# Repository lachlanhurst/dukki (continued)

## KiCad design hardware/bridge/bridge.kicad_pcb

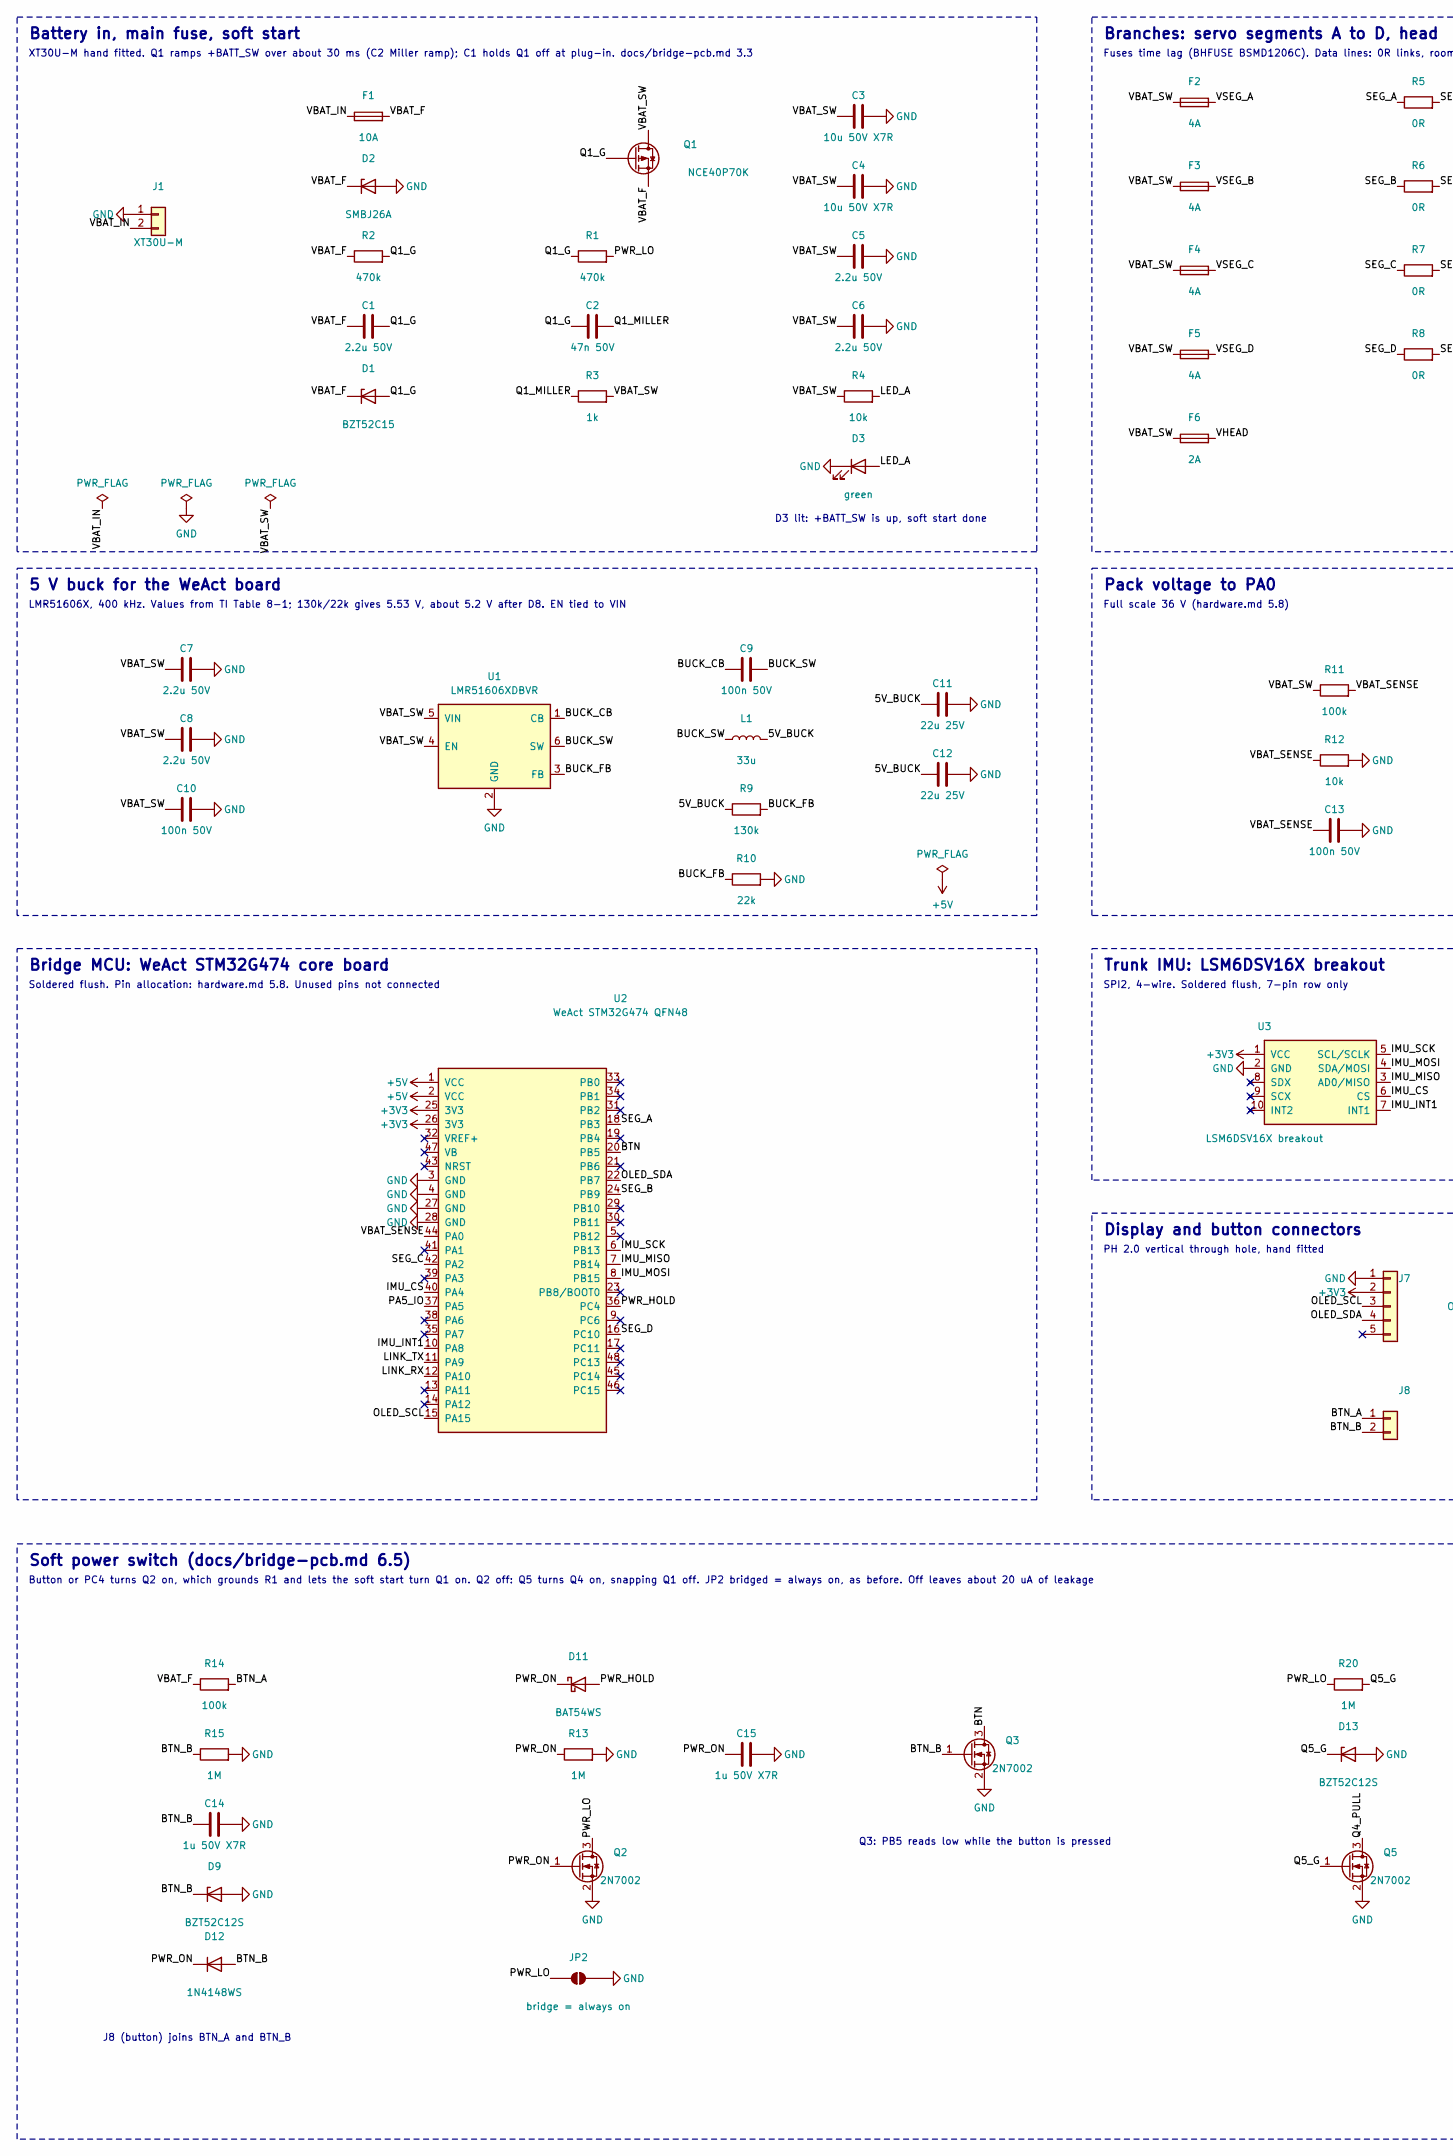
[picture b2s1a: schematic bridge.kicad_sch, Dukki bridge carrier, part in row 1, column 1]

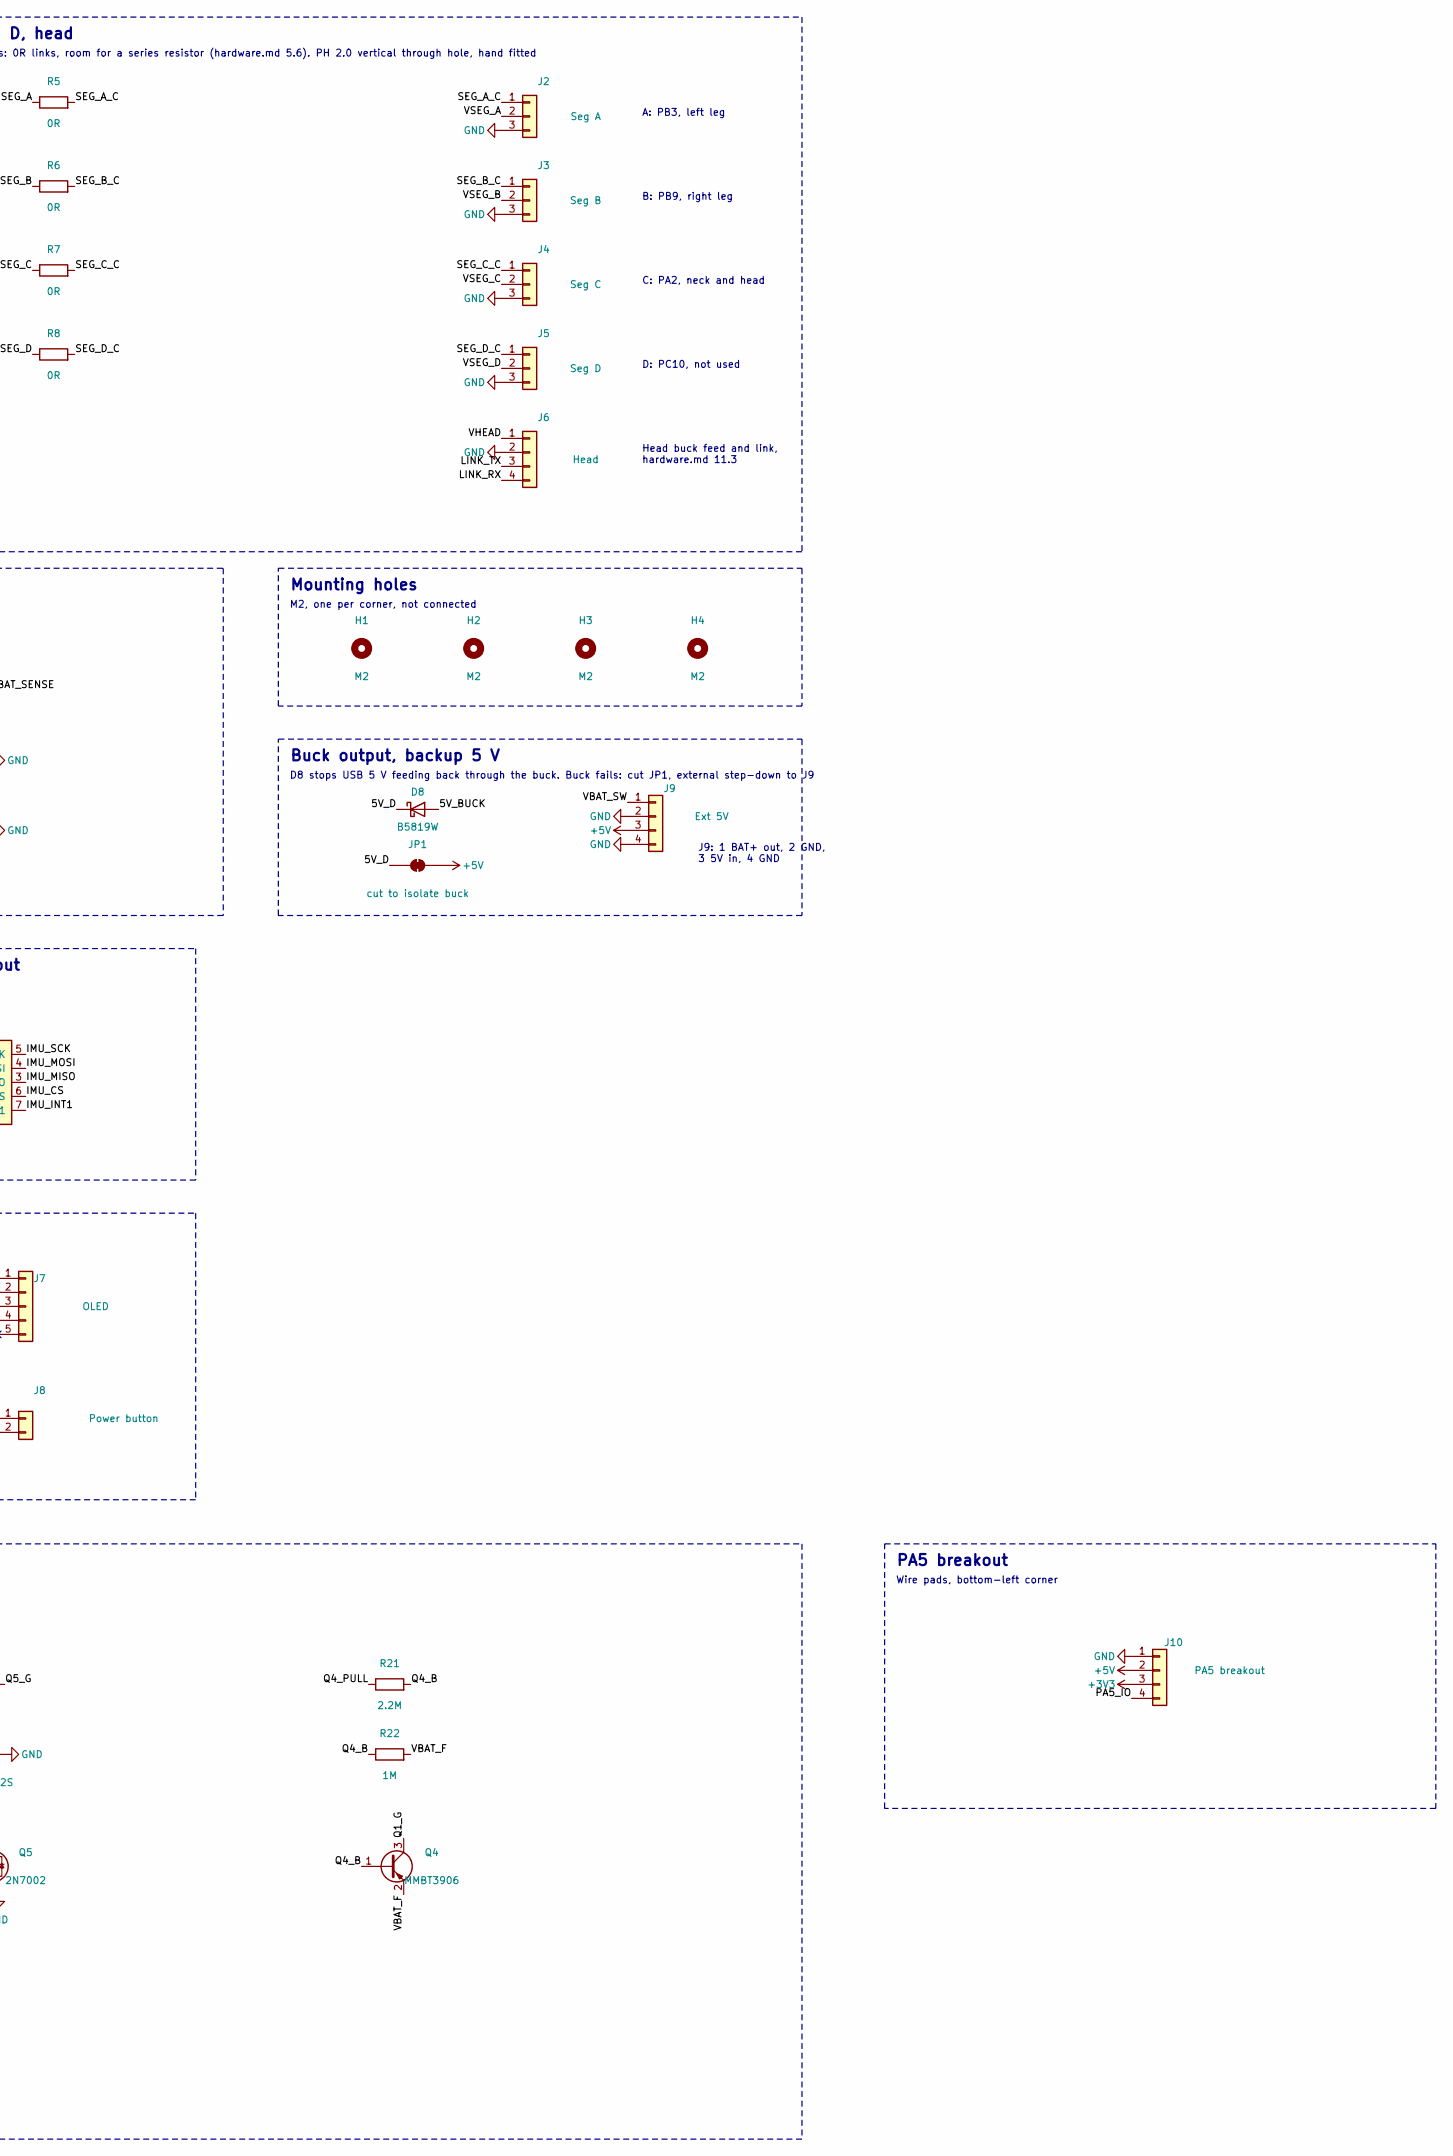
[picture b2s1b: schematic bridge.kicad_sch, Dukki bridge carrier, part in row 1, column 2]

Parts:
C1, C5, C6, C7, C8: 2.2u 50V; C_0805_2012Metric; LCSC C377773
C2: 47n 50V; C_0603_1608Metric; LCSC C1622
C3, C4: 10u 50V X7R; C_1210_3225Metric; LCSC C596319
C9, C10, C13: 100n 50V; C_0603_1608Metric; LCSC C14663
C11, C12: 22u 25V; C_0805_2012Metric; LCSC C45783
C14, C15: 1u 50V X7R; C_0805_2012Metric; LCSC C28323
D1: BZT52C15; D_SOD-123; LCSC C19077412
D2: SMBJ26A; D_SMB; LCSC C19077580
D3: green; LED_0603_1608Metric; LCSC C12624
D8: B5819W; D_SOD-123; LCSC C8598
D9, D13: BZT52C12S; D_SOD-323; LCSC C19077447
D11: BAT54WS; D_SOD-323; LCSC C7502694
D12: 1N4148WS; D_SOD-323; LCSC C2128
F1: 10A; Fuse_1206_3216Metric; MPN BHFUSE BSMD1206C-2100T, 10 A time lag, 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; LCSC C41367232
F2, F3, F4, F5: 4A; Fuse_1206_3216Metric; MPN BHFUSE BSMD1206C-1400T, 4 A time lag, 7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; LCSC C41367227
F6: 2A; Fuse_1206_3216Metric; MPN BHFUSE BSMD1206C-1200T, 2 A time lag, 7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; LCSC C41367223
H1, H2, H3, H4: M2; MountingHole_2.2mm_M2
J1: XT30U-M; AMASS_XT30U-M_1x02_P5.0mm_Vertical
J2: Seg A; JST_PH_B3B-PH-K_1x03_P2.00mm_Vertical; MPN JST B3B-PH-K-S, through hole, fitted by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
J3: Seg B; JST_PH_B3B-PH-K_1x03_P2.00mm_Vertical; MPN JST B3B-PH-K-S, through hole, fitted by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
J4: Seg C; JST_PH_B3B-PH-K_1x03_P2.00mm_Vertical; MPN JST B3B-PH-K-S, through hole, fitted by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
J5: Seg D; JST_PH_B3B-PH-K_1x03_P2.00mm_Vertical; MPN JST B3B-PH-K-S, through hole, fitted by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
J6: Head; JST_PH_B4B-PH-K_1x04_P2.00mm_Vertical; MPN JST B4B-PH-K-S, through hole, fitted by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
J7: OLED; JST_PH_B5B-PH-K_1x05_P2.00mm_Vertical; MPN JST B5B-PH-K-S, through hole, fitted by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
J8: Power button; JST_PH_B2B-PH-K_1x02_P2.00mm_Vertical; MPN JST B2B-PH-K-S, through hole, fitted by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
J9: Ext 5V; PinHeader_1x04_P2.54mm_Vertical
J10: PA5 breakout; PinHeader_1x04_P2.54mm_Vertical
JP1: cut to isolate buck; SolderJumper-2_P1.3mm_Bridged_RoundedPad1.0x1.5mm
JP2: bridge = always on; SolderJumper-2_P1.3mm_Open_RoundedPad1.0x1.5mm
L1: 33u; L_Sunlord_SWPA6045S; MPN Sunlord SWPA6045S330MT; LCSC C83451
Q1: NCE40P70K; TO-252-2; LCSC C130101
Q2, Q3, Q5: 2N7002; SOT-23; LCSC C8545
Q4: MMBT3906; SOT-23; LCSC C7420354
R1, R2: 470k; R_0603_1608Metric; LCSC C23178
R3: 1k; R_0603_1608Metric; LCSC C21190
R4, R12: 10k; R_0603_1608Metric; LCSC C25804
R5, R6, R7, R8: 0R; R_0603_1608Metric; LCSC C21189
R9: 130k; R_0603_1608Metric; LCSC C22795
R10: 22k; R_0603_1608Metric; LCSC C31850
R11, R14: 100k; R_0603_1608Metric; LCSC C25803
R13, R15, R20, R22: 1M; R_0603_1608Metric; LCSC C22935
R21: 2.2M; R_0603_1608Metric; LCSC C22938
U1: LMR51606XDBVR; SOT-23-6; LCSC C21260865
U2: WeAct STM32G474 QFN48; WeAct_STM32G474CoreBoard_QFN48
U3: LSM6DSV16X breakout; LSM6DSV16X_Breakout

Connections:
+3V3: J7.2, J10.3, U2.25 (3V3), U2.26 (3V3), U3.1 (VCC)
+5V: J9.3, J10.2, JP1.2 (B), U2.1 (VCC), U2.2 (VCC)
/5V_BUCK: C11.1, C12.1, D8.2 (A), L1.2, R9.1
/5V_D: D8.1 (K), JP1.1 (A)
/BTN: Q3.3 (D), U2.20 (PB5)
/BTN_A: J8.1, R14.2
/BTN_B: C14.1, D9.1 (K), D12.2 (A), J8.2, Q3.1 (G), R15.1
/BUCK_CB: C9.1, U1.1 (CB)
/BUCK_FB: R9.2, R10.1, U1.3 (FB)
/BUCK_SW: C9.2, L1.1, U1.6 (SW)
/IMU_CS: U2.40 (PA4), U3.6 (CS)
/IMU_INT1: U2.10 (PA8), U3.7 (INT1)
/IMU_MISO: U2.7 (PB14), U3.3 (AD0/MISO)
/IMU_MOSI: U2.8 (PB15), U3.4 (SDA/MOSI)
/IMU_SCK: U2.6 (PB13), U3.5 (SCL/SCLK)
/LED_A: D3.2 (A), R4.2
/LINK_RX: J6.4, U2.12 (PA10)
/LINK_TX: J6.3, U2.11 (PA9)
/OLED_SCL: J7.3, U2.15 (PA15)
/OLED_SDA: J7.4, U2.22 (PB7)
/PA5_IO: J10.4, U2.37 (PA5)
/PWR_HOLD: D11.2 (A), U2.36 (PC4)
/PWR_LO: JP2.1 (A), Q2.3 (D), R1.2, R20.1
/PWR_ON: C15.1, D11.1 (K), D12.1 (K), Q2.1 (G), R13.1
/Q1_G: C1.2, C2.1, D1.2 (A), Q1.1 (G), Q4.3 (C), R1.1, R2.2
/Q1_MILLER: C2.2, R3.1
/Q4_B: Q4.1 (B), R21.2, R22.1
/Q4_PULL: Q5.3 (D), R21.1
/Q5_G: D13.1 (K), Q5.1 (G), R20.2
/SEG_A: R5.1, U2.18 (PB3)
/SEG_A_C: J2.1, R5.2
/SEG_B: R6.1, U2.24 (PB9)
/SEG_B_C: J3.1, R6.2
/SEG_C: R7.1, U2.42 (PA2)
/SEG_C_C: J4.1, R7.2
/SEG_D: R8.1, U2.16 (PC10)
/SEG_D_C: J5.1, R8.2
/VBAT_F: C1.1, D1.1 (K), D2.1 (K), F1.2, Q1.3 (S), Q4.2 (E), R2.1, R14.1, R22.2
/VBAT_IN: F1.1, J1.2
/VBAT_SENSE: C13.1, R11.2, R12.1, U2.44 (PA0)
/VBAT_SW: C3.1, C4.1, C5.1, C6.1, C7.1, C8.1, C10.1, F2.1, F3.1, F4.1, F5.1, F6.1, J9.1, Q1.2 (D), R3.2, R4.1, R11.1, U1.4 (EN), U1.5 (VIN)
/VHEAD: F6.2, J6.1
/VSEG_A: F2.2, J2.2
/VSEG_B: F3.2, J3.2
/VSEG_C: F4.2, J4.2
/VSEG_D: F5.2, J5.2
GND: C3.2, C4.2, C5.2, C6.2, C7.2, C8.2, C10.2, C11.2, C12.2, C13.2, C14.2, C15.2, D2.2 (A), D3.1 (K), D9.2 (A), D13.2 (A), J1.1, J2.3, J3.3, J4.3, J5.3, J6.2, J7.1, J9.2, J9.4, J10.1, JP2.2 (B), Q2.2 (S), Q3.2 (S), Q5.2 (S), R10.2, R12.2, R13.2, R15.2, U1.2 (GND), U2.3 (GND), U2.4 (GND), U2.27 (GND), U2.28 (GND), U3.2 (GND)

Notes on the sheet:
Battery in, main fuse, soft start
XT30U-M hand fitted. Q1 ramps +BATT_SW over about 30 ms (C2 Miller ramp); C1 holds Q1 off at plug-in. docs/bridge-pcb.md 3.3
D3 lit: +BATT_SW is up, soft start done
Branches: servo segments A to D, head
Fuses time lag (BHFUSE BSMD1206C). Data lines: 0R links, room for a series resistor (hardware.md 5.6). PH 2.0 vertical through hole, hand fitted
A: PB3, left leg
B: PB9, right leg
C: PA2, neck and head
D: PC10, not used
Head buck feed and link, hardware.md 11.3
5 V buck for the WeAct board
LMR51606X, 400 kHz. Values from TI Table 8-1; 130k/22k gives 5.53 V, about 5.2 V after D8. EN tied to VIN
Pack voltage to PA0
Full scale 36 V (hardware.md 5.8)
Mounting holes
M2, one per corner, not connected
Buck output, backup 5 V
D8 stops USB 5 V feeding back through the buck. Buck fails: cut JP1, external step-down to J9
J9: 1 BAT+ out, 2 GND, 3 5V in, 4 GND
Bridge MCU: WeAct STM32G474 core board
Soldered flush. Pin allocation: hardware.md 5.8. Unused pins not connected
Trunk IMU: LSM6DSV16X breakout
SPI2, 4-wire. Soldered flush, 7-pin row only
Display and button connectors
PH 2.0 vertical through hole, hand fitted
Soft power switch (docs/bridge-pcb.md 6.5)
Button or PC4 turns Q2 on, which grounds R1 and lets the soft start turn Q1 on. Q2 off: Q5 turns Q4 on, snapping Q1 off. JP2 bridged = always on, as before. Off leaves about 20 uA of leakage
J8 (button) joins BTN_A and BTN_B
Q3: PB5 reads low while the button is pressed
PA5 breakout
Wire pads, bottom-left corner

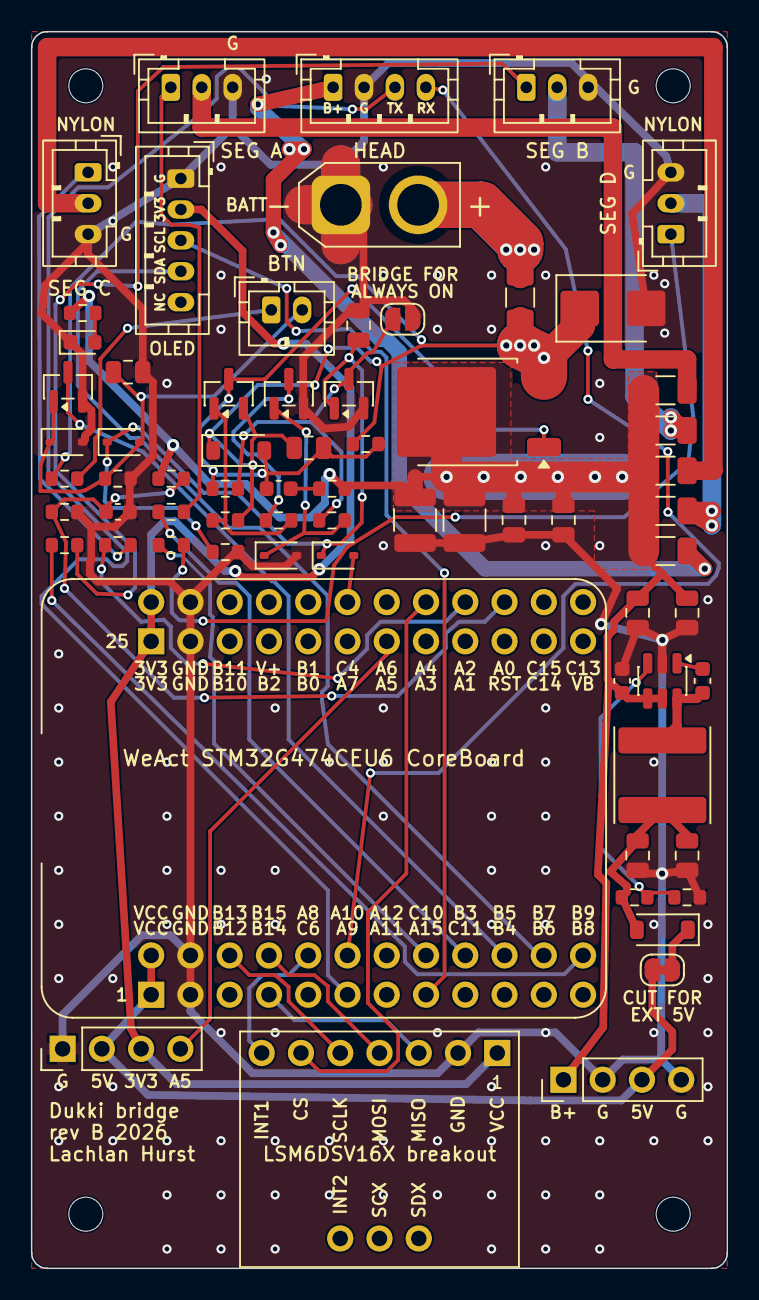
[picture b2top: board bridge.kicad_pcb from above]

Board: 2 copper layers, 45.0 x 80.0 mm, 72 parts (0 on the bottom side), 47 nets.

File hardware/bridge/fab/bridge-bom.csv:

Comment,Designator,Footprint,LCSC Part #
2.2u 50V,"C1,C5,C6,C7,C8",C_0805_2012Metric,C377773
47n 50V,C2,C_0603_1608Metric,C1622
10u 50V X7R,"C3,C4",C_1210_3225Metric,C596319
100n 50V,"C9,C10,C13",C_0603_1608Metric,C14663
22u 25V,"C11,C12",C_0805_2012Metric,C45783
1u 50V X7R,"C14,C15",C_0805_2012Metric,C28323
BZT52C15,D1,D_SOD-123,C19077412
SMBJ26A,D2,D_SMB,C19077580
green,D3,LED_0603_1608Metric,C12624
B5819W,D8,D_SOD-123,C8598
BZT52C12S,"D9,D13",D_SOD-323,C19077447
BAT54WS,D11,D_SOD-323,C7502694
1N4148WS,D12,D_SOD-323,C2128
10A,F1,Fuse_1206_3216Metric,C41367232
4A,"F2,F3,F4,F5",Fuse_1206_3216Metric,C41367227
2A,F6,Fuse_1206_3216Metric,C41367223
33u,L1,L_Sunlord_SWPA6045S,C83451
NCE40P70K,Q1,TO-252-2,C130101
2N7002,"Q2,Q3,Q5",SOT-23,C8545
MMBT3906,Q4,SOT-23,C7420354
470k,"R1,R2",R_0603_1608Metric,C23178
1k,R3,R_0603_1608Metric,C21190
10k,"R4,R12",R_0603_1608Metric,C25804
0R,"R5,R6,R7,R8",R_0603_1608Metric,C21189
130k,R9,R_0603_1608Metric,C22795
22k,R10,R_0603_1608Metric,C31850
100k,"R11,R14",R_0603_1608Metric,C25803
1M,"R13,R15,R20,R22",R_0603_1608Metric,C22935
2.2M,R21,R_0603_1608Metric,C22938
LMR51606XDBVR,U1,SOT-23-6,C21260865

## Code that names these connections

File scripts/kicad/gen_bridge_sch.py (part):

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R("R2", "470k", 78.74, 58.42, "VBAT_F", "Q1_G")
C("C1", "2.2u 50V", 78.74, 71.12, "VBAT_F", "Q1_G", fp=C0805, lcsc="C377773")
part("Device:D_Zener", "D1", "BZT52C15", 78.74, 83.82, {"1": "VBAT_F", "2": "Q1_G"}, footprint="Diode_SMD:D_SOD-123", lcsc="C19077412")
part("Dukki:Q_PMOS_GDS", "Q1", "NCE40P70K", 127, 40.64, {"1": "Q1_G", "2": "VBAT_SW", "3": "VBAT_F"}, rot=0,
     footprint="Package_TO_SOT_SMD:TO-252-2", lcsc="C130101", ref_at=(137.16, 38.1), val_at=(142.24, 43.18))
R("R1", "470k", 119.38, 58.42, "Q1_G", "PWR_LO")     # to ground through the power switch (Q2) or JP2
C("C2", "47n 50V", 119.38, 71.12, "Q1_G", "Q1_MILLER", lcsc="C1622")
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# 2. Branches: servo segments and head ---------------------------------------------------
box(210, 15, 405, 112, "Branches: servo segments A to D, head",
    "Fuses time lag (BHFUSE BSMD1206C). Data lines: 0R links, room for a series resistor (hardware.md 5.6). PH 2.0 vertical through hole, hand fitted")
SEGS = [("A", "PB3, left leg"), ("B", "PB9, right leg"), ("C", "PA2, neck and head"), ("D", "PC10, not used")]
for i, (s, what) in enumerate(SEGS):
    y = 30.48 + i * 15.24
    part("Device:Fuse", f"F{2 + i}", "4A", 228.6, y, {"1": "VBAT_SW", "2": f"VSEG_{s}"}, footprint=F1206, lcsc="C41367227",
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                                          ("C10", "100n 50V", C0603, "C14663")]):
    C(ref, val, 45.72, 133.35 + i * 12.7, "VBAT_SW", "GND", fp=fp, lcsc=lc)
part("Dukki:LMR51606", "U1", "LMR51606XDBVR", 101.6, 147.32,
     {"CB": "BUCK_CB", "GND": "GND", "FB": "BUCK_FB", "EN": "VBAT_SW", "VIN": "VBAT_SW", "SW": "BUCK_SW"}, rot=0,
     footprint="Package_TO_SOT_SMD:SOT-23-6", lcsc="C21260865", ref_at=(101.6, 134.62), val_at=(101.6, 137.16))
C("C9", "100n 50V", 147.32, 133.35, "BUCK_CB", "BUCK_SW", lcsc="C14663")
part("Device:L", "L1", "33u", 147.32, 146.05, {"1": "BUCK_SW", "2": "5V_BUCK"}, footprint="Inductor_SMD:L_Sunlord_SWPA6045S",
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flag("+5V", 182.88, 171.45)

# 4. Pack voltage --------------------------------------------------------------------------
box(210, 115, 300, 178, "Pack voltage to PA0", "Full scale 36 V (hardware.md 5.8)")
R("R11", "100k", 254, 137.16, "VBAT_SW", "VBAT_SENSE")
R("R12", "10k", 254, 149.86, "VBAT_SENSE", "GND")
C("C13", "100n 50V", 254, 162.56, "VBAT_SENSE", "GND", lcsc="C14663")
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     rot=0, footprint="Jumper:SolderJumper-2_P1.3mm_Bridged_RoundedPad1.0x1.5mm", in_bom=False,
     ref_at=(335.28, 165.1), val_at=(335.28, 173.99))
part("Connector_Generic:Conn_01x04", "J9", "Ext 5V", 378.46, 160.02,
     {"1": "VBAT_SW", "2": "GND", "3": "+5V", "4": "GND"}, rot=0,
     footprint="Connector_PinHeader_2.54mm:PinHeader_1x04_P2.54mm_Vertical", in_bom=False,
     ref_at=(381.0, 154.94), val_at=(388.62, 160.02),
     extra={"Note": "Wire pads: 1 BAT+ (switched rail) and 2 GND to the external step-down input, 3 5V and 4 GND from its output"})
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box(15, 184, 200, 284, "Bridge MCU: WeAct STM32G474 core board",
    "Soldered flush. Pin allocation: hardware.md 5.8. Unused pins not connected")
MCU = {"VCC": "+5V", "GND": "GND", "3V3": "+3V3",
       "PA9": "LINK_TX", "PA10": "LINK_RX", "PB3": "SEG_A", "PB9": "SEG_B", "PA2": "SEG_C", "PC10": "SEG_D",
       "PB13": "IMU_SCK", "PB14": "IMU_MISO", "PB15": "IMU_MOSI", "PA4": "IMU_CS", "PA8": "IMU_INT1",
       "PA0": "VBAT_SENSE", "PA15": "OLED_SCL", "PB7": "OLED_SDA", "PB5": "BTN",
       "PC4": "PWR_HOLD", "PA5": "PA5_IO"}
wpins = pins_of(lib_block("WeAct_STM32G474CoreBoard", "WeAct_STM32G474CoreBoard_QFN48"))
mnets = {num: MCU.get(v[3]) for num, v in wpins.items()}
part("WeAct_STM32G474CoreBoard:WeAct_STM32G474CoreBoard_QFN48", "U2", "WeAct STM32G474 QFN48", 106.68, 238.76, mnets,
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box(210, 184, 295, 226, "Trunk IMU: LSM6DSV16X breakout", "SPI2, 4-wire. Soldered flush, 7-pin row only")
part("LSM6DSV16X_Breakout:LSM6DSV16X_Breakout", "U3", "LSM6DSV16X breakout", 251.46, 208.28,
     {"VCC": "+3V3", "GND": "GND", "SCL/SCLK": "IMU_SCK", "SDA/MOSI": "IMU_MOSI", "AD0/MISO": "IMU_MISO",
      "CS": "IMU_CS", "INT1": "IMU_INT1", "SDX": None, "SCX": None, "INT2": None}, rot=0,
     footprint="LSM6DSV16X_Breakout:LSM6DSV16X_Breakout", in_bom=False, ref_at=(241.3, 198.12), val_at=(241.3, 218.44))

# 8. Display and button --------------------------------------------------------------------
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
# 9. Soft power switch ----------------------------------------------------------------------
box(15, 292, 405, 400, "Soft power switch (docs/bridge-pcb.md 6.5)",
    "Button or PC4 turns Q2 on, which grounds R1 and lets the soft start turn Q1 on. Q2 off: Q5 turns Q4 on, "
    "snapping Q1 off. JP2 bridged = always on, as before. Off leaves about 20 uA of leakage")
# button input: pack-fed through R14; the contacts switch about 30 uA; D9 clamps the button side to 12 V,
# C14 and R15 debounce the sense; C15 on PWR_ON (below) stretches a tap until the bridge has booted.
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part("Device:D_Schottky", "D11", "BAT54WS", 116.84, 317.5, {"1": "PWR_ON", "2": "PWR_HOLD"},
     footprint="Diode_SMD:D_SOD-323", lcsc="C7502694")
R("R13", "1M", 116.84, 330.2, "PWR_ON", "GND")
# hold-up: with R13 about 1 s, so Q2 stays on through a bridge reset until the firmware re-asserts PC4
C("C15", "1u 50V X7R", 147.32, 330.2, "PWR_ON", "GND", fp=C0805, lcsc="C28323")
part("Transistor_FET:Q_NMOS_GSD", "Q2", "2N7002", 116.84, 350.52, {"1": "PWR_ON", "2": "GND", "3": "PWR_LO"},
     rot=0, footprint="Package_TO_SOT_SMD:SOT-23", lcsc="C8545", ref_at=(124.46, 347.98), val_at=(124.46, 353.06))
part("Jumper:SolderJumper_2_Open", "JP2", "bridge = always on", 116.84, 370.84, {"1": "PWR_LO", "2": "GND"}, rot=0,
     footprint="Jumper:SolderJumper-2_P1.3mm_Open_RoundedPad1.0x1.5mm", in_bom=False,
     ref_at=(116.84, 367.03), val_at=(116.84, 375.92))
# button sense for the bridge: PB5 sees only its pull-up and Q3, low while pressed (as on the breadboard)
part("Transistor_FET:Q_NMOS_GSD", "Q3", "2N7002", 187.96, 330.2, {"1": "BTN_B", "2": "GND", "3": "BTN"},
     rot=0, footprint="Package_TO_SOT_SMD:SOT-23", lcsc="C8545", ref_at=(195.58, 327.66), val_at=(195.58, 332.74))
text("Q3: PB5 reads low while the button is pressed", 167.64, 345.44)
# fast turn-off: with Q2 off, PWR_LO rises to Q1's gate, Q5 turns on and Q4 pulls Q1's gate to its source
R("R20", "1M", 256.54, 317.5, "PWR_LO", "Q5_G")
part("Device:D_Zener", "D13", "BZT52C12S", 256.54, 330.2, {"1": "Q5_G", "2": "GND"},
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part("Transistor_BJT:Q_PNP_BEC", "Q4", "MMBT3906", 330.2, 350.52, {"1": "Q4_B", "2": "VBAT_F", "3": "Q1_G"},
     rot=0, footprint="Package_TO_SOT_SMD:SOT-23", lcsc="C7420354", ref_at=(337.82, 347.98), val_at=(337.82, 353.06))

# 10. PA5 breakout ---------------------------------------------------------------------------
box(420, 292, 520, 340, "PA5 breakout", "Wire pads, bottom-left corner")
part("Connector_Generic:Conn_01x04", "J10", "PA5 breakout", 469.9, 314.96,
     {"1": "GND", "2": "+5V", "3": "+3V3", "4": "PA5_IO"}, rot=0,
     footprint="Connector_PinHeader_2.54mm:PinHeader_1x04_P2.54mm_Vertical", in_bom=False,
     ref_at=(472.44, 309.88), val_at=(482.6, 314.96))

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
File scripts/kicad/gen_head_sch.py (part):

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    "Pin allocation: docs/head-pcb.md section 4. Unused pins not connected, as on the NANO-A")
CM4 = {"58": "I2C8_SDA", "56": "I2C8_SCL", "47": "UART7_TX", "45": "UART7_RX", "50": "FAN_PWM",
       "44": "EYE_DATA", "49": "SAI2_SCLK", "26": "SAI2_LRCK", "25": "SAI2_SDO", "27": "SAI2_SDI",
       "35": "CAM_SCL", "36": "CAM_SDA", "97": "CAM_GPIO", "78": "CM4_3V3", "84": "CM4_3V3",
       "128": "CSI_D0_N", "130": "CSI_D0_P", "134": "CSI_D1_N", "136": "CSI_D1_P",
       "140": "CSI_C_N", "142": "CSI_C_P"}
CM4.update({str(n): "+5V" for n in (77, 79, 81, 83, 85, 87)})
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# USB2 OTG0, the RK3576's download port (Radxa sheet 22: 103 USB2_OTG0_DM, 105 USB2_OTG0_DP), to bottom
# test pads for maskrom flashing in place; the module holds its own VBUSDET high (sheet 8, R134)
CM4.update({"103": "USB_DN", "105": "USB_DP"})
# GPIO7 (pin 37, RK3576 GPIO1_C0, PWM0_CH0_M1) to a bottom test pad, for a possible mouth servo on its own
# buck later. On J9's outer row, so it escapes easily; PWM0, not the fan's PWM1, so its period is its own
CM4.update({"37": "SERVO_PWM"})
CM4.update({"31": "SPI2_CLK", "28": "SPI2_MOSI", "46": "SPI2_MISO", "54": "SPI2_CS0", "30": "SPI_INT", "34": "SPI_IO"})
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     footprint="Capacitor_SMD:CP_Elec_6.3x7.7", lcsc="C970679", extra={"MPN": "RVT1H470M0607, 47 uF 50 V aluminium, 6.3 x 7.7 mm"})
C("C4", "100n 50V", 279.4, 101.6, "VBAT_IN", "GND")
part("DukkiHead:LMR51635", "U2", "LMR51635YDDCR", 304.8, 50.8,
     {"CB": "BUCK_CB", "GND": "GND", "FB": "BUCK_FB", "EN": "VBAT_IN", "VIN": "VBAT_IN", "SW": "BUCK_SW"}, rot=0,
     footprint="Package_TO_SOT_SMD:TSOT-23-6", lcsc="C45262770", ref_at=(304.8, 38.1), val_at=(304.8, 40.64))
C("C5", "100n 50V", 345.44, 35.56, "BUCK_CB", "BUCK_SW")
part("Device:L", "L1", "4.7u", 345.44, 48.26, {"1": "BUCK_SW", "2": "5V_BUCK"}, footprint="Inductor_SMD:L_Sunlord_SWPA6045S",
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    "JP3 feeds it: cut JP3 to use an external amplifier module on J11")
part("DukkiHead:MAX98357A", "U4", "MAX98357AETE+T", 472.44, 114.3,
     {"DIN": "SAI2_SDO", "BCLK": "SAI2_SCLK", "LRCLK": "SAI2_LRCK", "~{SD_MODE}": "AMP_SD", "GAIN_SLOT": "AMP_GAIN",
      "VDD": "AMP_5V", "GND": "GND", "PAD": "GND", "NC": None, "OUTP": "SPK_P", "OUTN": "SPK_N"}, rot=0,
     footprint="Package_DFN_QFN:TQFN-16-1EP_3x3mm_P0.5mm_EP1.23x1.23mm", lcsc="C910544",
     ref_at=(472.44, 97.79), val_at=(472.44, 100.33))
R("R3", "1M", 431.8, 132.08, "AMP_5V", "AMP_SD")
part("Jumper:SolderJumper_2_Bridged", "JP3", "cut for ext amp", 431.8, 90.17, {"1": "+5V", "2": "AMP_5V"}, rot=0,
     footprint="DukkiHead:SolderJumper-2_Wide_Bridged_3A", in_bom=False, ref_at=(431.8, 86.36), val_at=(431.8, 95.25))
R("R4", "100k", 515.62, 132.08, "AMP_GAIN", "GND", dnp=True)
C("C12", "10u 25V", 515.62, 93.98, "AMP_5V", "GND")
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box(195, 118, 395, 178, "Fan and eye LED", "Fan: low side, PWM1_CH2 (pin 50). Eye: WS2812-type, SPI1 MOSI (pin 44), 3.3 V data")
R("R5", "100R", 223.52, 147.32, "FAN_PWM", "FAN_G")
R("R6", "100k", 243.84, 160.02, "FAN_G", "GND")
part("Transistor_FET:AO3400A", "Q1", "AO3400A", 266.7, 147.32, {"G": "FAN_G", "S": "GND", "D": "FAN_N"}, rot=0,
     footprint="Package_TO_SOT_SMD:SOT-23", lcsc="C20917", ref_at=(274.32, 144.78), val_at=(274.32, 149.86))
part("Device:D_Schottky", "D2", "B5819W", 297.18, 134.62, {"1": "+5V", "2": "FAN_N"},
     footprint="Diode_SMD:D_SOD-123", lcsc="C8598")
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     extra={"Note": "Generic BMI088 module, hand fitted on short header pins; PS link on IIC"})
  PH("J2", "ToF", 4, 330.2, 213.36, {"1": "GND", "2": "+3V3", "3": "I2C8_SDA", "4": "I2C8_SCL"}, "VL53L8CX breakout,\nQwiic order")
  part("Connector_Generic:Conn_01x04", "J3", "I2C pins", 330.2, 241.3,
     {"1": "GND", "2": "+3V3", "3": "I2C8_SDA", "4": "I2C8_SCL"}, rot=0,
     footprint="Connector_PinHeader_2.00mm:PinHeader_1x04_P2.00mm_Vertical", in_bom=False,
     ref_at=(332.74, 233.68), val_at=(340.36, 241.3),
     extra={"Note": "Pin holes at 2.0 mm (a B4B-PH-K header fits): G, 3V3, SDA, SCL"})
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  C("C15", "100n 50V", 289.56, 233.68, "+3V3", "GND")
  C("C16", "100n 50V", 289.56, 246.38, "+3V3", "GND")
  text("C15 at VDD, C16 at VDDIO", 279.4, 251.46)
  part("Jumper:SolderJumper_2_Bridged", "JP4", "cut for ext IMU", 223.52, 279.4, {"1": "I2C8_SDA", "2": "IMU_SDA"}, rot=0,
       footprint="Jumper:SolderJumper-2_P1.3mm_Bridged_RoundedPad1.0x1.5mm", in_bom=False,
       ref_at=(223.52, 275.59), val_at=(223.52, 284.48))
  part("Jumper:SolderJumper_2_Bridged", "JP5", "cut for ext IMU", 254.0, 279.4, {"1": "I2C8_SCL", "2": "IMU_SCL"}, rot=0,
       footprint="Jumper:SolderJumper-2_P1.3mm_Bridged_RoundedPad1.0x1.5mm", in_bom=False,
       ref_at=(254.0, 275.59), val_at=(254.0, 284.48))
  R("R8", "4.7k", 289.56, 208.28, "+3V3", "I2C8_SDA")
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
# 8. Camera ----------------------------------------------------------------------------------
box(405, 196, 585, 290, "Camera FPC",
    "Pi 15-pin camera order. CAM0 lanes (Radxa CSI1), I2C6 with 4.7k pull-ups, CAM_GPIO enable. 100 ohm pairs")
part("Connector_Generic_MountingPin:Conn_01x15_MountingPin", "J8", "Camera", 477.52, 243.84,
     {"1": "GND", "2": "CSI_D0_N", "3": "CSI_D0_P", "4": "GND", "5": "CSI_D1_N", "6": "CSI_D1_P", "7": "GND",
      "8": "CSI_C_N", "9": "CSI_C_P", "10": "GND", "11": "CAM_GPIO", "12": None, "13": "CAM_SCL", "14": "CAM_SDA",
      "15": "+3V3", "MP": "GND"}, rot=0,
     footprint="DukkiHead:FPC_XUNPU_FPC-1.0HF-15PWAR-H20_1x15-1MP_P1.0mm", lcsc="C19269369",
     extra={"MPN": "XUNPU FPC-1.0HF-15PWAR-H20, dual contact"}, ref_at=(480.06, 220.98), val_at=(480.06, 266.7))
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    ("; J11 is bottom-side solder pads, between the IMU module's pin rows" if EXT else
     ". J3 (section 6) takes an external IMU module"))
part("Connector_Generic:Conn_01x04", "J12", "Ext 5V", 449.58, 330.2,
     {"1": "VBAT_IN", "2": "GND", "3": "+5V", "4": "GND"}, rot=0,
     footprint="Connector_PinHeader_2.54mm:PinHeader_1x04_P2.54mm_Vertical", in_bom=False,
     ref_at=(452.12, 322.58), val_at=(459.74, 330.2),
     extra={"Note": "Wire pads: 1 B+ and 2 GND to the external step-down input, 3 5V and 4 GND from its output"})
text("J12: 1 B+ out, 2 GND,\n3 5V in, 4 GND", 467.36, 327.66)
part("Connector_Generic:Conn_01x07", "J11", "Ext amp", 449.58, 360.68,
     {"1": "SAI2_LRCK", "2": "SAI2_SCLK", "3": "SAI2_SDO", "4": None, "5": None, "6": "GND", "7": "+5V"}, rot=0,
     footprint="DukkiHead:SolderPads_1x07_P2.54mm_AMP" if EXT else "Connector_PinHeader_2.54mm:PinHeader_1x07_P2.54mm_Vertical",
     in_bom=False,
     ref_at=(452.12, 349.25), val_at=(459.74, 360.68),
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# 11. SPI breakout ----------------------------------------------------------------------------
box(195, 344, 395, 400, "SPI breakout",
    "SPI2 M1 for a future SPI device, untested. Wire pads on the bottom, under the module, along the top edge.\n"
    "CLK GPIO12 (CM4 31), MOSI GPIO13 (28), MISO GPIO22 (46), CS0 GPIO4 (54), INT GPIO6 (30), spare GPIO5 (34)")
part("Connector_Generic:Conn_01x09", "J13", "SPI pads", 238.76, 375.92,
     {"1": "GND", "2": "+5V", "3": "+3V3", "4": "SPI2_MOSI", "5": "SPI2_MISO", "6": "SPI2_CLK", "7": "SPI2_CS0",
      "8": "SPI_INT", "9": "SPI_IO"}, rot=0,
     footprint="DukkiHead:SolderPads_1x09_P2.54mm_SPI", in_bom=False, ref_at=(241.3, 361.95), val_at=(248.92, 375.92),
     extra={"Note": "Bottom-side wire pads: G, 5V, 3V3, MO, MI, CK, CS, INT, IO"})
text("J13: 1 GND, 2 5V, 3 3V3, 4 MOSI, 5 MISO,\n6 CLK, 7 CS0, 8 INT, 9 spare GPIO", 256.54, 373.38)
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# 12. Link series resistors, test pads --------------------------------------------------------
box(405, 384, 585, 416, "Link series resistors, test pads",
    "Series R in each UART7 line: 1k on RX limits current into an unpowered CM4 from the bridge, 330R on TX. TP1/TP2 (bottom): short to TP3 to reset; hold TP2 low through a reset for maskrom.\n"
    "TP4-TP6 (bottom): USB D-, D+, GND of the download port, for rkdeveloptool in maskrom. TP7: GPIO7 / PWM0_CH0_M1 (pin 37) for a servo")
R("R13", "1k", 431.8, 400.05, "UART7_RX", "LINK_RX")     # 1k: the bridge drives this line into a halted CM4 (2.7 mA, not 8)
R("R14", "330R", 459.74, 400.05, "UART7_TX", "LINK_TX")
for i, (ref, net) in enumerate((("TP1", "CM4_RESET"), ("TP2", "CM4_MASKROM"), ("TP3", "GND"))):
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
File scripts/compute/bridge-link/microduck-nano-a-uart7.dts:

// UART7 on the Waveshare CM4-NANO-A header with a Radxa CM4 (RK3576), for the servo bridge link.
//
//   header pin 16  GPIO23 position -> GPIO2_B6, UART7_TX_M0  -> bridge PA10 (USART1_RX)
//   header pin 18  GPIO24 position -> GPIO2_B7, UART7_RX_M0  <- bridge PA9 (USART1_TX)
//
// The link is full duplex, 3.3 V on both sides, no flow control, 2 Mbps (hardware.md 5.5).
// duck-control's BridgeIo opens the port robotd.toml names in [bus] port, /dev/ttyS7 on the vendor
// kernel.
//
// Armbian user overlay: compiled and installed by scripts/compute/setup-bridge-link.sh into
// /boot/overlay-user/ and named in user_overlays= in /boot/armbianEnv.txt.

/dts-v1/;
/plugin/;

/ {
	metadata {
		title = "UART7 on the CM4-NANO-A header, pins 16 and 18";
		compatible = "radxa,cm4-io";
		category = "misc";
		exclusive = "GPIO2_B6", "GPIO2_B7";
		description = "Radxa CM4 on Waveshare CM4-NANO-A: UART7 M0 on header pins 16 (TX) and 18 (RX) for the servo bridge.";
	};
};

&uart7 {
	status = "okay";
	pinctrl-names = "default";
	pinctrl-0 = <&uart7m0_xfer>;
};

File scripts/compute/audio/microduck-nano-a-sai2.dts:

// SAI2 on the Waveshare CM4-NANO-A header with a Radxa CM4 (RK3576), for the head speaker and
// microphone. No codec chip: both parts are plain I2S breakouts.
//
//   header pin 12  GPIO18 position -> GPIO1_D1, SAI2_SCLK_M0  bit clock   -> MAX98357A BCLK, INMP441 SCK
//   header pin 35  GPIO19 position -> GPIO1_D2, SAI2_LRCK_M0  frame clock -> MAX98357A LRC,  INMP441 WS
//   header pin 40  GPIO21 position -> GPIO1_D0, SAI2_SDO_M0   data out    -> MAX98357A DIN
//   header pin 38  GPIO20 position -> GPIO1_D3, SAI2_SDI_M0   data in     <- INMP441 SD
//
// The SAI is bit and frame master. The codec side is Rockchip's dummy codec, built into the
// vendor kernel, which accepts any format and has no controls. The base tree's sai2 node already
// selects the M0 pins without MCLK (neither part needs it), so pin 36 stays free.
//
// Slots are fixed at 32 bits, so BCLK is 64 x fs whatever the sample format. The INMP441 needs
// 64 clocks per frame; the MAX98357A accepts 32, 48 or 64. The mic is a left-slot part (L/R to
// ground) and the amplifier mixes (L + R) / 2 by default.
//
// Armbian user overlay: compiled and installed by scripts/compute/setup-audio.sh into
// /boot/overlay-user/ and named in user_overlays= in /boot/armbianEnv.txt. The card registers
// as ALSA card "microduck".

/dts-v1/;
/plugin/;

/ {
	metadata {
		title = "SAI2 I2S audio on the CM4-NANO-A header";
		compatible = "radxa,cm4-io";
		category = "audio";
		exclusive = "GPIO1_D0", "GPIO1_D1", "GPIO1_D2", "GPIO1_D3";
		description = "Radxa CM4 on Waveshare CM4-NANO-A: SAI2 M0 on header pins 12, 35, 38 and 40 with a dummy codec, for a MAX98357A amplifier and an INMP441 microphone.";
	};
};

&{/} {
	microduck_codec: microduck-codec {
		compatible = "rockchip,dummy-codec";
		#sound-dai-cells = <0>;
		status = "okay";
	};

	microduck-sound {
		compatible = "simple-audio-card";
		simple-audio-card,name = "microduck";
		simple-audio-card,format = "i2s";
		simple-audio-card,mclk-fs = <256>;
		simple-audio-card,bitclock-master = <&microduck_cpu>;
		simple-audio-card,frame-master = <&microduck_cpu>;
		status = "okay";

		microduck_cpu: simple-audio-card,cpu {
			sound-dai = <&sai2>;
			dai-tdm-slot-num = <2>;
			dai-tdm-slot-width = <32>;
		};

		simple-audio-card,codec {
			sound-dai = <&microduck_codec>;
		};
	};
};

&sai2 {
	status = "okay";
};
